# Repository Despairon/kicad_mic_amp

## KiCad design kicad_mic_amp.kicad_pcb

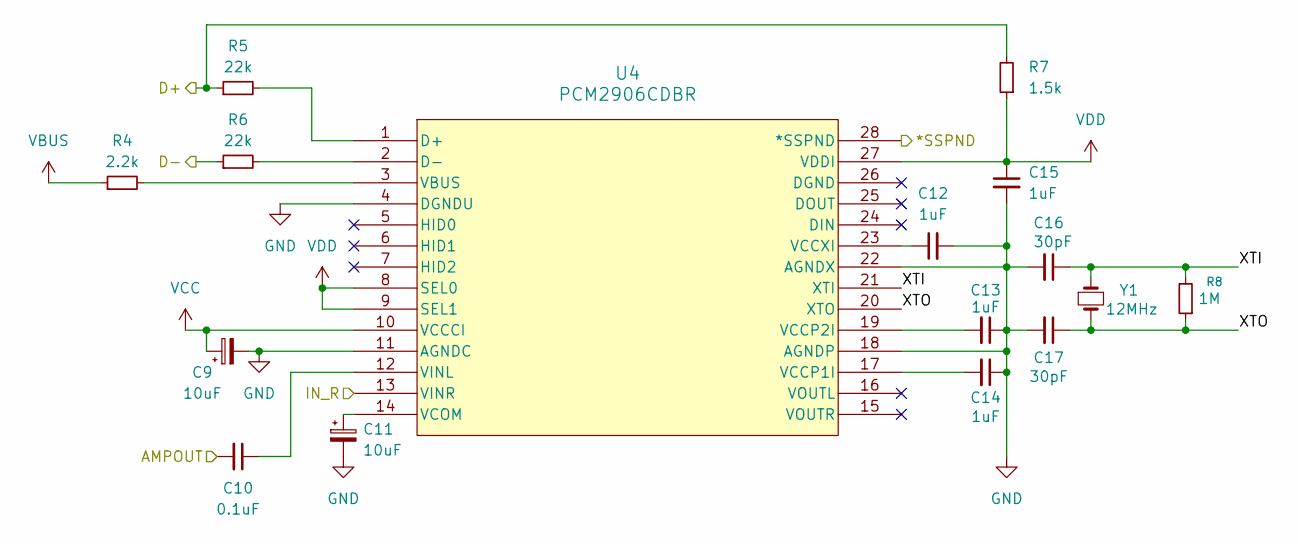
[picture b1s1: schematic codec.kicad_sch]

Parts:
C9, C11: 10uF; CP_EIA-3216-10_Kemet-I_HandSolder
C10: 0.1uF; C_0603_1608Metric_Pad1.08x0.95mm_HandSolder
C12, C13, C14, C15: 1uF; C_0603_1608Metric_Pad1.08x0.95mm_HandSolder
C16, C17: 30pF; C_0603_1608Metric_Pad1.08x0.95mm_HandSolder
R4: 2.2k; R_0603_1608Metric_Pad0.98x0.95mm_HandSolder
R5, R6: 22k; R_0603_1608Metric_Pad0.98x0.95mm_HandSolder
R7: 1.5k; R_0603_1608Metric_Pad0.98x0.95mm_HandSolder
R8: 1M; R_0603_1608Metric_Pad0.98x0.95mm_HandSolder
U4: PCM2906CDBR; DB28_TEX
Y1: 12MHz; Crystal_HC49-4H_Vertical

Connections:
/Amplifier/*SSPND: U4.28 (*SSPND); also elsewhere on the board
/Amplifier/AMPOUT: C10.2; also elsewhere on the board
/Codec/D+: R5.1, R7.2; also elsewhere on the board
/Codec/D-: R6.1; also elsewhere on the board
/Codec/IN_R: U4.13 (VINR); also elsewhere on the board
/Codec/XTI: C16.1, R8.2, U4.21 (XTI), Y1.1
/Codec/XTO: C17.1, R8.1, U4.20 (XTO), Y1.2
GND: C9.2, C11.2, C12.2, C13.1, C14.1, C15.2, C16.2, C17.2, U4.4 (DGNDU), U4.11 (AGNDC), U4.18 (AGNDP), U4.22 (AGNDX); also elsewhere on the board
unnamed: R5.2, U4.1 (D+)
unnamed: R6.2, U4.2 (D-)
unnamed: R4.2, U4.3 (VBUS)
unnamed: C14.2, U4.17 (VCCP1I)
unnamed: C13.2, U4.19 (VCCP2I)
unnamed: C12.1, U4.23 (VCCXI)
unnamed: C11.1, U4.14 (VCOM)
unnamed: C10.1, U4.12 (VINL)
VBUS: R4.1; also elsewhere on the board
VCC: C9.1, U4.10 (VCCCI); also elsewhere on the board
VDD: C15.1, R7.1, U4.8 (SEL0), U4.9 (SEL1), U4.27 (VDDI)

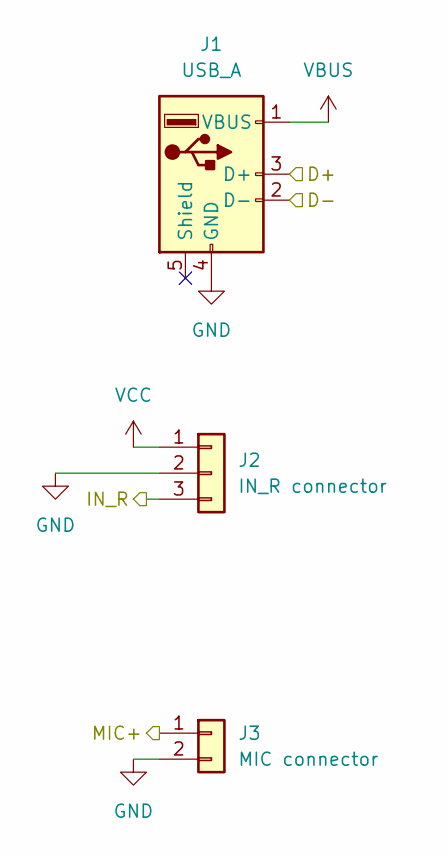
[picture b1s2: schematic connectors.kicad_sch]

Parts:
J1: USB_A; USB3_A_Molex_48393-001
J2: IN_R connector; PinHeader_1x03_P1.27mm_Vertical
J3: MIC connector; PinHeader_1x02_P1.27mm_Vertical

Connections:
/Amplifier/MIC+: J3.1; also elsewhere on the board
/Codec/D+: J1.3 (D+); also elsewhere on the board
/Codec/D-: J1.2 (D-); also elsewhere on the board
/Codec/IN_R: J2.3; also elsewhere on the board
GND: J1.4 (GND), J2.2, J3.2; also elsewhere on the board
VBUS: J1.1 (VBUS); also elsewhere on the board
VCC: J2.1; also elsewhere on the board

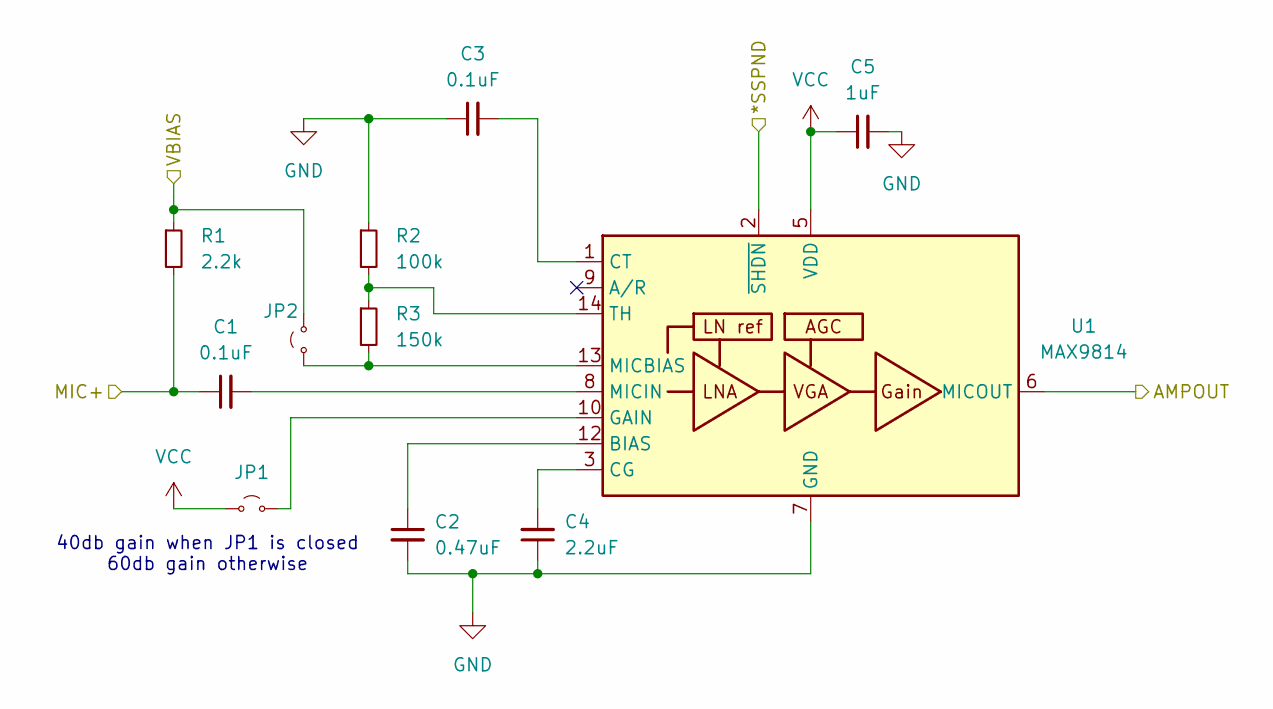
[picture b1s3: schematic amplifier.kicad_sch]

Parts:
C1, C3: 0.1uF; C_0603_1608Metric_Pad1.08x0.95mm_HandSolder
C2: 0.47uF; C_0603_1608Metric_Pad1.08x0.95mm_HandSolder
C4: 2.2uF; C_0603_1608Metric_Pad1.08x0.95mm_HandSolder
C5: 1uF; C_0603_1608Metric_Pad1.08x0.95mm_HandSolder
JP1, JP2: PinHeader_1x02_P1.27mm_Vertical
R1: 2.2k; R_0603_1608Metric_Pad0.98x0.95mm_HandSolder
R2: 100k; R_0603_1608Metric_Pad0.98x0.95mm_HandSolder
R3: 150k; R_0603_1608Metric_Pad0.98x0.95mm_HandSolder
U1: MAX9814; DFN-14-1EP_3x3mm_P0.4mm_EP1.78x2.35mm

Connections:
/Amplifier/*SSPND: U1.2 (~SHDN); also elsewhere on the board
/Amplifier/AMPOUT: U1.6 (MICOUT); also elsewhere on the board
/Amplifier/MIC+: C1.1, R1.2; also elsewhere on the board
/Amplifier/VBIAS: JP2.2 (B), R1.1; also elsewhere on the board
GND: C2.2, C3.1, C4.1, C5.2, R2.1, U1.4 (GND), U1.7 (GND), U1.11 (GND), U1.15 (GND); also elsewhere on the board
unnamed: JP1.2 (B), U1.10 (GAIN)
unnamed: JP2.1 (A), R3.2, U1.13 (MICBIAS)
unnamed: C2.1, U1.12 (BIAS)
unnamed: C4.2, U1.3 (CG)
unnamed: C3.2, U1.1 (CT)
unnamed: C1.2, U1.8 (MICIN)
unnamed: R2.2, R3.1, U1.14 (TH)
VCC: C5.1, JP1.1 (A), U1.5 (VDD); also elsewhere on the board

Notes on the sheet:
40db gain when JP1 is closed 60db gain otherwise

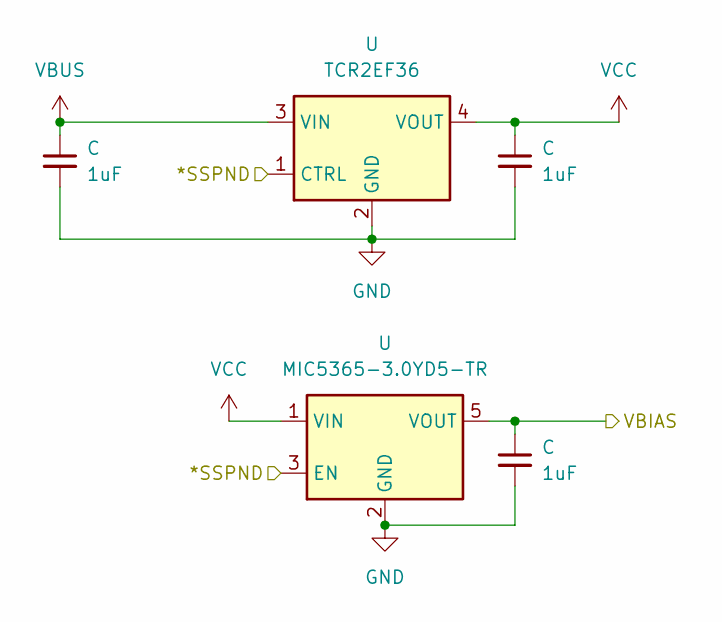
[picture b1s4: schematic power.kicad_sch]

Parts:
C: 1uF; C_0603_1608Metric_Pad1.08x0.95mm_HandSolder
U: TCR2EF36; SOT-553

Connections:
unnamed: C.1, U.1 (VIN), U.3 (EN), U.4 (NC), U.5 (VOUT)
unnamed: C.2, U.2 (GND)
unnamed: U.1 (VIN), U.3 (EN)

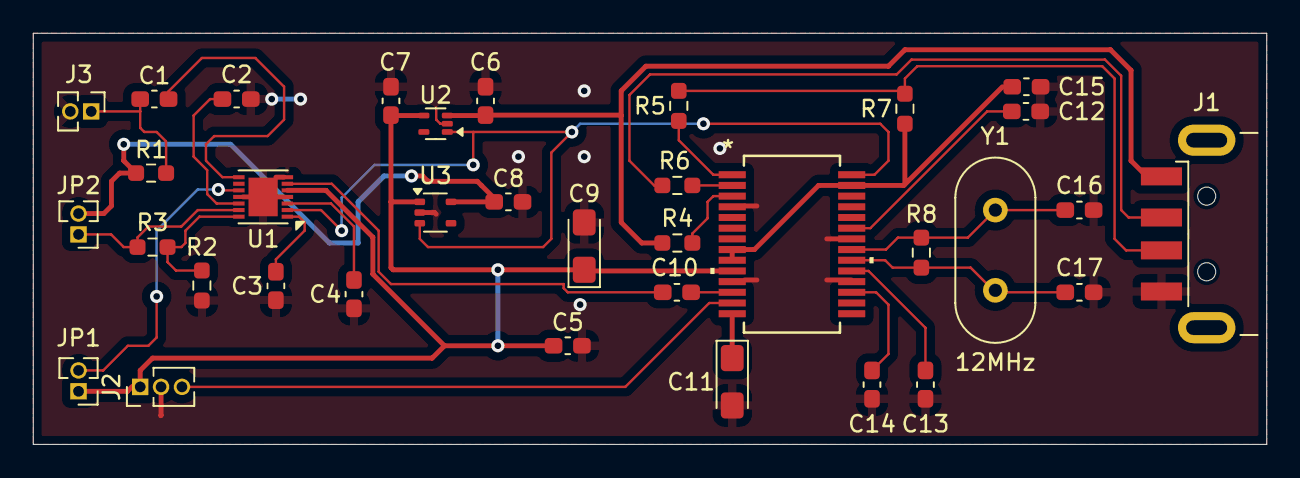
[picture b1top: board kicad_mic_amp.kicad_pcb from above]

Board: 2 copper layers, 75.0 x 25.0 mm, 35 parts (0 on the bottom side), 28 nets.

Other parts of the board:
C6, C7, C8: 1uF; C_0603_1608Metric_Pad1.08x0.95mm_HandSolder
U2: TCR2EF36; SOT-553
U3: MIC5365-3.0YD5-TR; SOT-353_SC-70-5

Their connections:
/Amplifier/*SSPND: U2.1 (CTRL), U3.3 (EN); also elsewhere on the board
/Amplifier/VBIAS: C8.1, U3.5 (VOUT); also elsewhere on the board
GND: C6.2, C7.2, C8.2, U2.2 (GND), U3.2 (GND); also elsewhere on the board
VBUS: C6.1, U2.3 (VIN); also elsewhere on the board
VCC: C7.1, U2.4 (VOUT), U3.1 (VIN); also elsewhere on the board

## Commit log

2025-05-29 Move the project to GIT (So far done amp, power, and codec.)
2025-05-29 Added Connectors; added hierarchical labels connections
2025-05-29 Added screenshots of the schematics
2025-06-04 Add missing PCM2906 components; Partially Implement PCB
2025-06-04 Add PCB changes
2025-06-05 Finish the PCB. Needs double check
2025-06-05 Correct PCB; Correct Root sheet; add PCB and 3D View pictures
